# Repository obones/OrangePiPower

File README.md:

PIC16F628A
  - Pin 5 (VSS) to ground
  - Pin 6 (RB0) towards mosfet Gate
  - Pin 7 (RB1) to ground to emulate false "powerloss" on bootup
  - Pin 11 (RB5) to ground to emilate "pi running" on bootup
  - Pin 14 (VDD) to +5V
  - Pin 18 (AN1) to potentiometer center point

FQP50N06  (G D S)
  - Gate to pin 6 (RB0) to drive the relay (emulated by a LED)
  - Source to ground
  - Drain to charge (LED -> resistor -> 5V)
  - 1k resitor between Gate and Source to avoid a floating gate

Potentiometer
  - Center to pin 18 (AN1) for duration
  - Top to +5
  - Bottom to GND

2N3904 in OpenCollector configuration towards PiRunning (E B C - flat fat towards you)
  - E to ground
  - B to controlled signal --> PA9
  - C to PiRunning (Pin 11 - RB5)
  - Pull down resistor between B and E (ground) 6.8k
Or 2N7000 in Open Drain configuration towards PiRunning (S G D - flat face towards you)
  - S to ground
  - G to controlled signal --> PA9
  - D to PiRunning (Pin 11 - RB5)
  - Pull down resistor between G and S (ground) 1k

BSS88 as a protection on PowerLoss on the OrangePi side
  - D to PowerLoss from OrangePiPower
  - G to 3.3V
  - S to OrangePi pin

From AN97055 via https://electronics.stackexchange.com/questions/82104/single-transistor-level-up-shifter

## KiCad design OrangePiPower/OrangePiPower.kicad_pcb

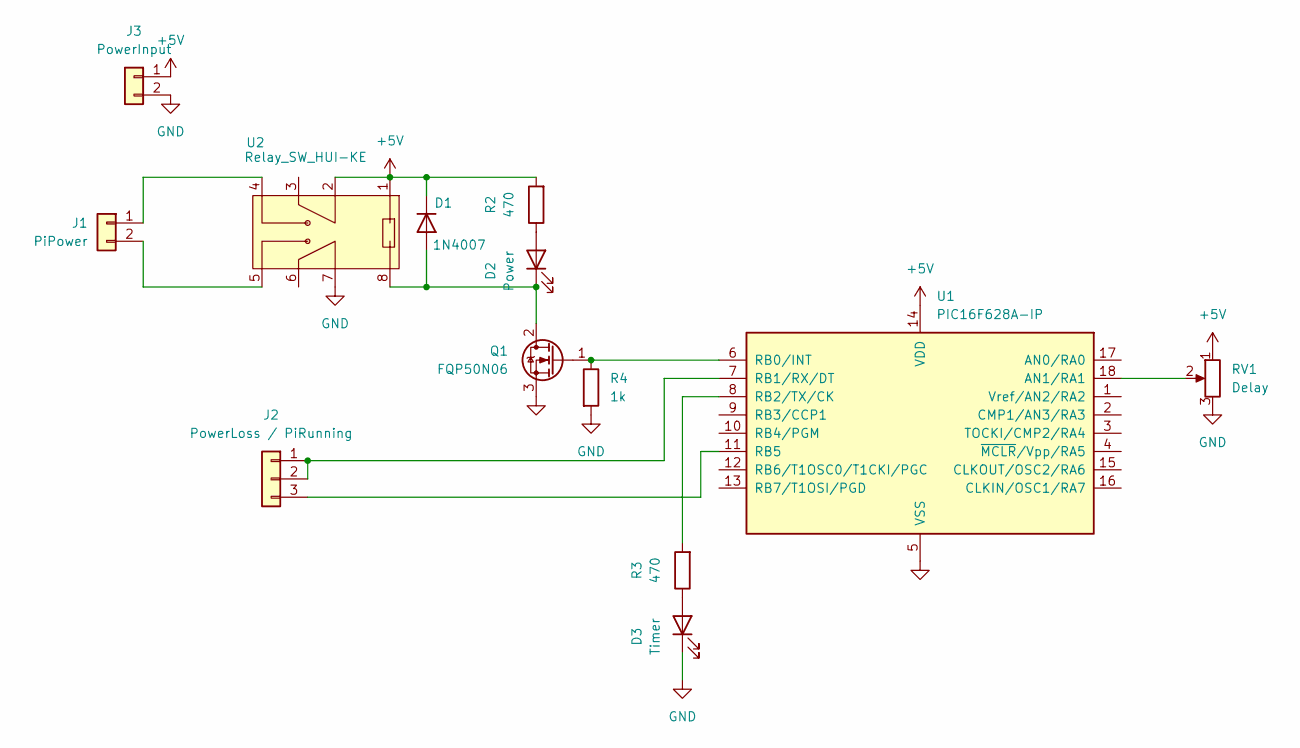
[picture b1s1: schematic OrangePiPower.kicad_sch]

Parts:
D1: 1N4007; D_DO-41_SOD81_P10.16mm_Horizontal
D2: Power; LED_D3.0mm_Clear
D3: Timer; LED_D3.0mm_Clear
J1: PiPower; PinHeader_1x02_P2.54mm_Vertical
J2: PowerLoss / PiRunning; PinHeader_1x03_P2.54mm_Vertical
J3: PowerInput; PinHeader_1x02_P2.54mm_Vertical
Q1: FQP50N06; TO-220-3_Vertical
R2, R3: 470; R_Axial_DIN0204_L3.6mm_D1.6mm_P5.08mm_Horizontal
R4: 1k; R_Axial_DIN0204_L3.6mm_D1.6mm_P5.08mm_Horizontal
RV1: Delay; POT_3386G
U1: PIC16F628A-IP; DIP-18_W7.62mm_LongPads
U2: Relay_SW_HUI-KE; Relay_HUI-KE

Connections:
+5V: D1.1 (K), J3.1, R2.2, RV1.1, U1.14 (VDD), U2.1, U2.2
GND: D3.1 (K), J3.2, Q1.3 (S), R4.2, RV1.3, U1.5 (VSS), U2.7
unnamed: D1.2 (A), D2.1 (K), Q1.2 (D), U2.8
unnamed: D2.2 (A), R2.1
unnamed: D3.2 (A), R3.1
unnamed: J1.1, U2.4
unnamed: J1.2, U2.5
unnamed: J2.1, J2.2, U1.7 (RB1/RX/DT)
unnamed: J2.3, U1.11 (RB5)
unnamed: Q1.1 (G), R4.1, U1.6 (RB0/INT)
unnamed: RV1.2, U1.18 (AN1/RA1)
unnamed: R3.2, U1.8 (RB2/TX/CK)

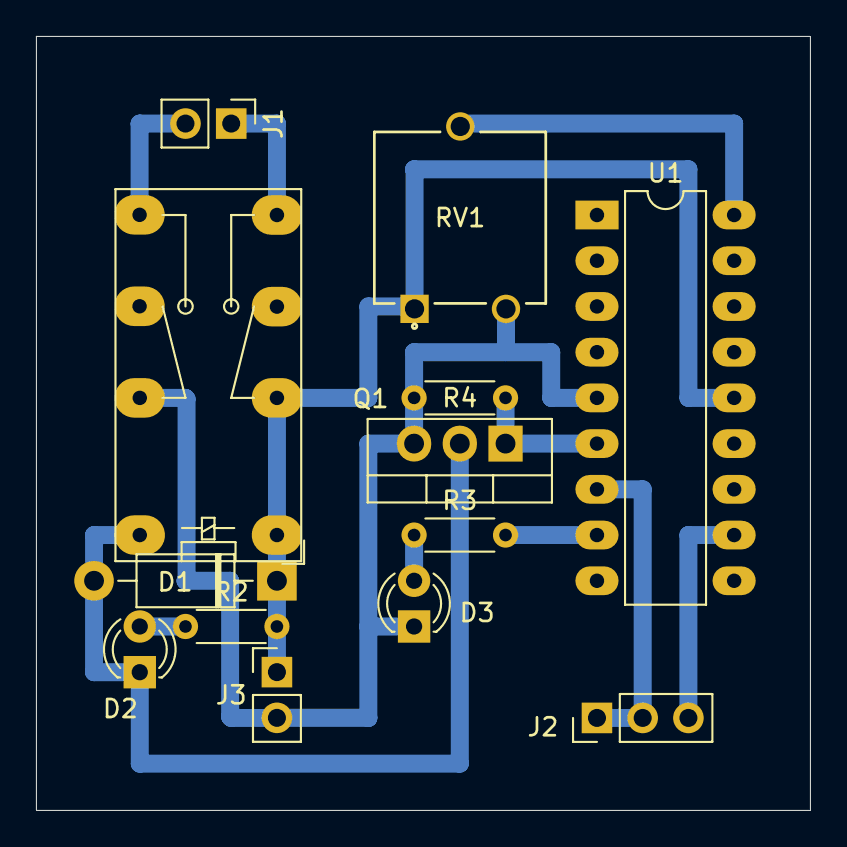
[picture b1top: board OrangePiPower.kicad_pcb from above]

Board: 2 copper layers, 43.0 x 43.0 mm, 13 parts (0 on the bottom side), 12 nets.

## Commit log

2025-07-12 feat: initial content
2025-07-12 feat: 3D model for the final PCB
